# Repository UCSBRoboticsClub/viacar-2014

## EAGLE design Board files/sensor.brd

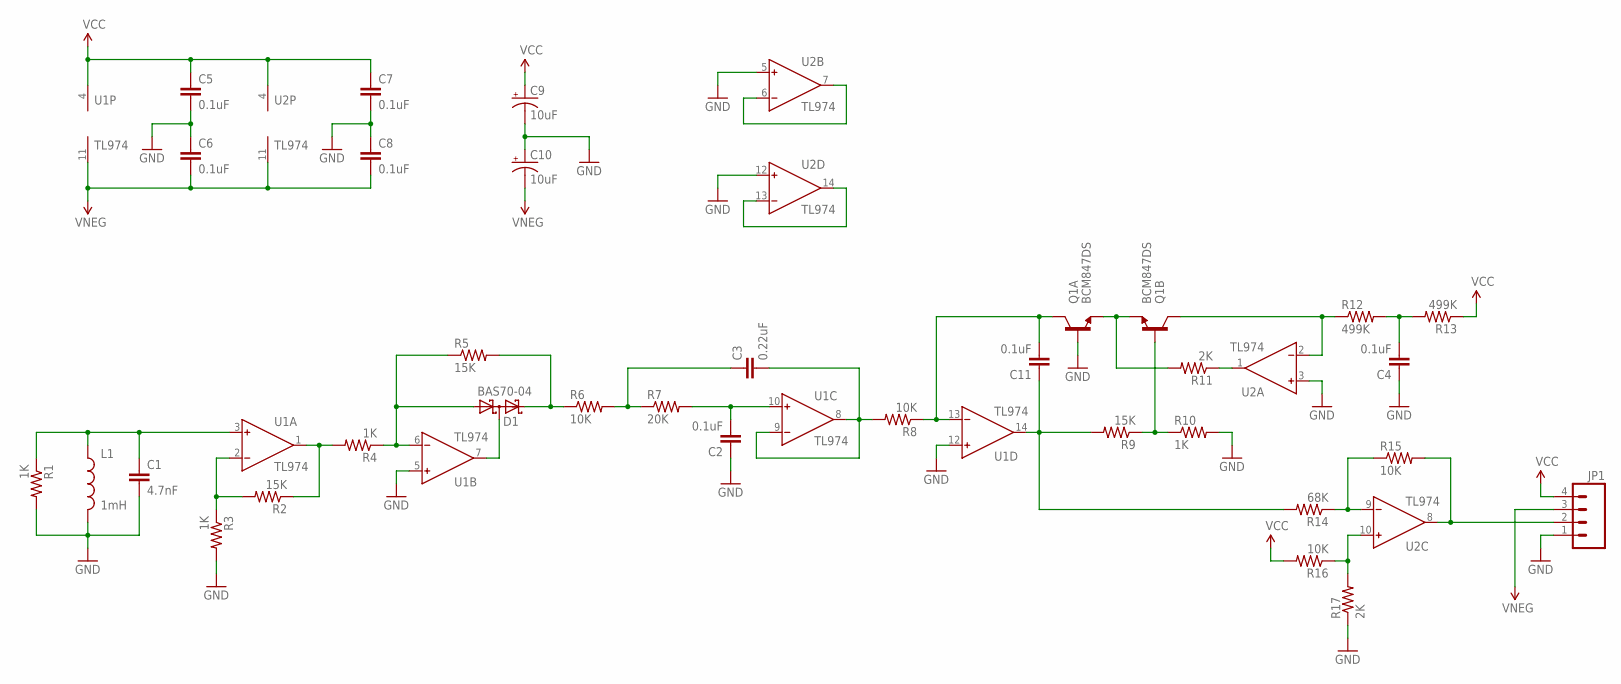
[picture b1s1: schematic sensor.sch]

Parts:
C1: 4.7nF; 0805
C2, C4, C5, C6, C7, C8, C11: 0.1uF; 0805
C3: 0.22uF; 0805
C9, C10: 10uF; E2-4
D1: BAS70-04; SOT23
JP1: M04POLAR_LOCK; MOLEX-1X4_LOCK
L1: 1mH; RLB0912
Q1: BCM847DS; SOT-457
R1, R3, R4, R10: 1K; 0805
R2, R5, R9: 15K; 0805
R6, R8, R15, R16: 10K; 0805
R7: 20K; 0805
R11, R17: 2K; 0805
R12, R13: 499K; 0805
R14: 68K; 0805
U1, U2: TL974; SOIC-14

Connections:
GND: C1.2, C2.1, C4.1, C5.2, C6.1, C7.2, C8.1, C9.-, C10.+, JP1.1, L1.2, Q1.2 (B), R1.2, R3.2, R10.2, R17.1, U1.5 (IN+), U1.12 (IN+), U2.3 (IN+), U2.5 (IN+), U2.12 (IN+)
unnamed: C1.1, L1.1, R1.1, U1.3 (IN+)
unnamed: D1.1 (A1), R4.1, R5.1, U1.6 (IN-)
unnamed: R2.2, R3.1, U1.2 (IN-)
unnamed: R2.1, R4.2, U1.1 (OUT)
unnamed: D1.2 (C2), R5.2, R6.1
unnamed: C2.2, R7.2, U1.10 (IN+)
unnamed: C3.1, R6.2, R7.1
unnamed: D1.3 (C1A2), U1.7 (OUT)
unnamed: U2.6 (IN-), U2.7 (OUT)
unnamed: C3.2, R8.2, U1.8 (OUT), U1.9 (IN-)
unnamed: U2.13 (IN-), U2.14 (OUT)
unnamed: C11.2, Q1.6 (C), R8.1, U1.13 (IN-)
unnamed: R11.1, U2.1 (OUT)
unnamed: Q1.1 (E), Q1.4 (E), R11.2
unnamed: Q1.5 (B), R9.1, R10.1
unnamed: C11.1, R9.2, R14.2, U1.14 (OUT)
unnamed: C4.2, R12.2, R13.2
unnamed: Q1.3 (C), R12.1, U2.2 (IN-)
unnamed: R16.1, R17.2, U2.10 (IN+)
unnamed: R14.1, R15.1, U2.9 (IN-)
unnamed: JP1.2, R15.2, U2.8 (OUT)
VCC: C5.1, C7.1, C9.+, JP1.4, R13.1, R16.2, U1.4 (V+), U2.4 (V+)
VNEG: C6.2, C8.2, C10.-, JP1.3, U1.11 (V-), U2.11 (V-)

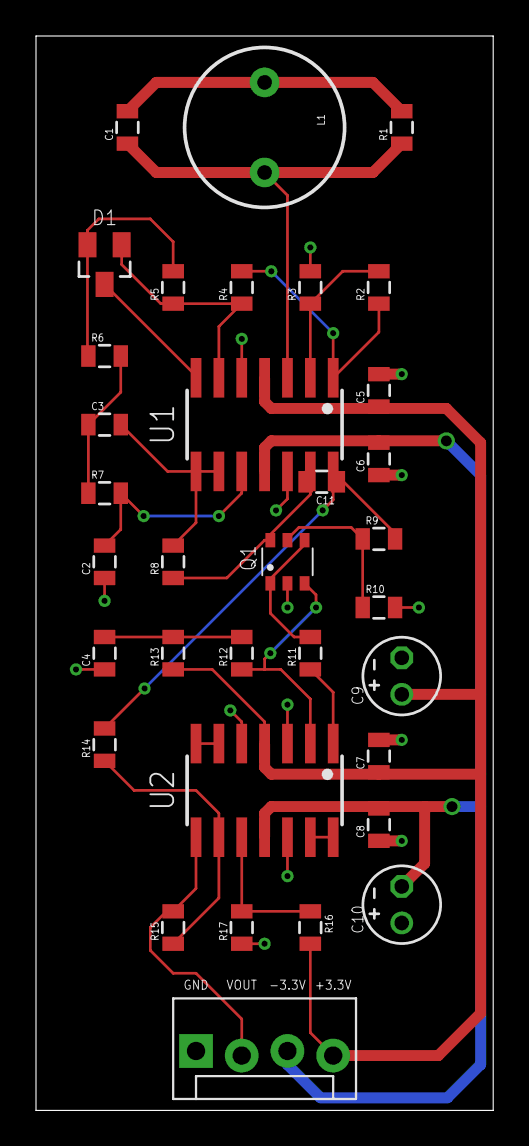
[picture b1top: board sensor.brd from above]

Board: 2 copper layers, 25.4 x 59.7 mm, 34 parts (0 on the bottom side), 24 nets.

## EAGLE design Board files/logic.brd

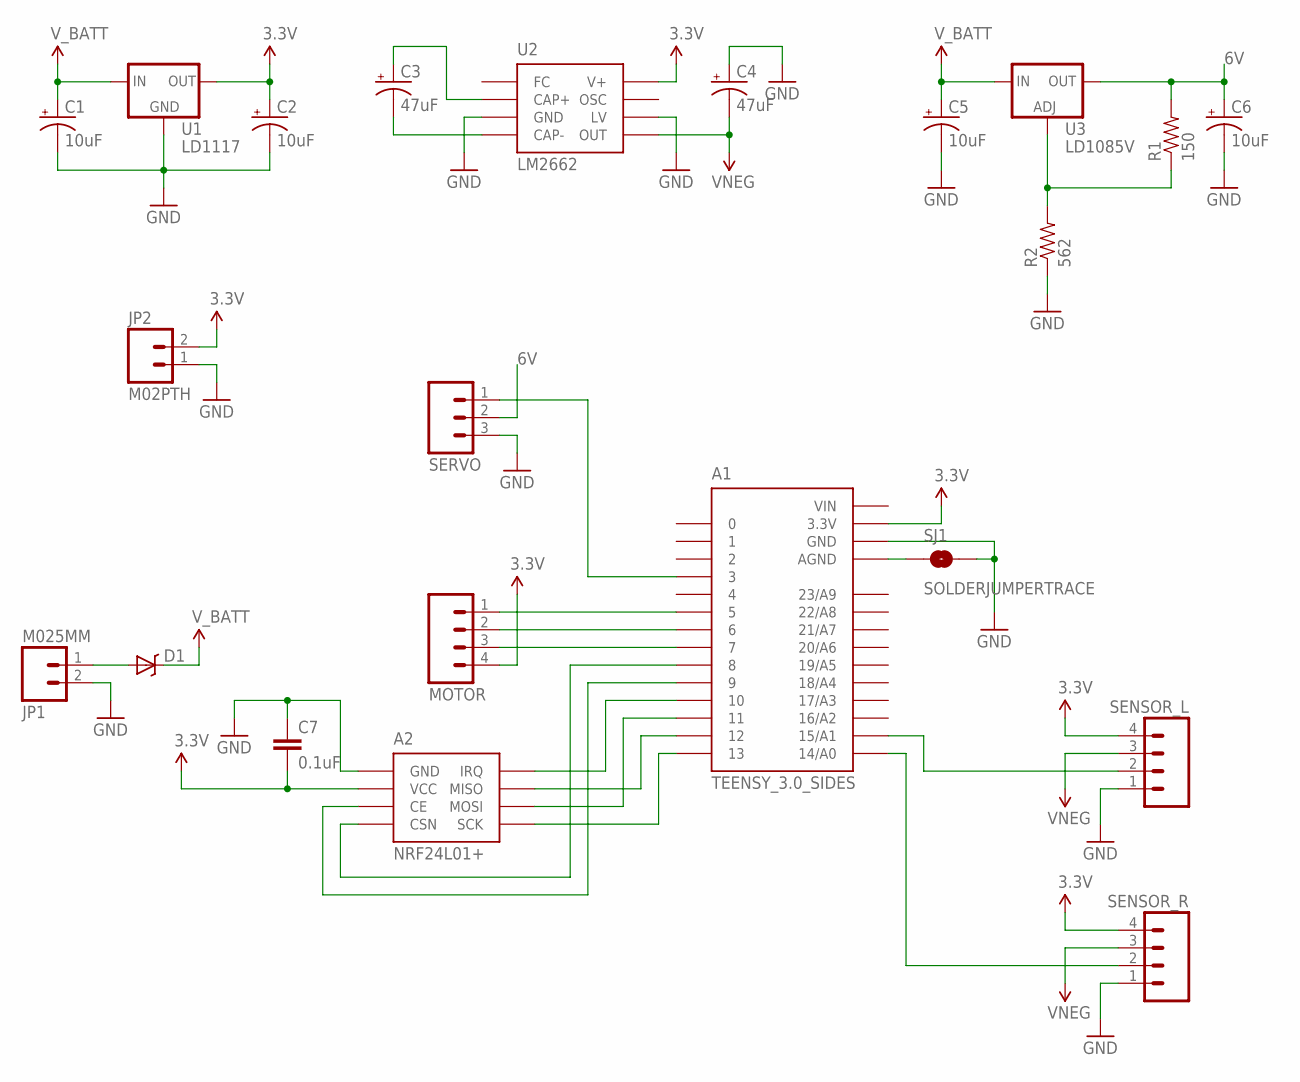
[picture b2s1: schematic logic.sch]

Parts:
A1: TEENSY_3.0_SIDES
A2: NRF24L01+
C1, C2, C5, C6: 10uF; E2-4
C3, C4: 47uF; CPOL-RADIAL-100UF-25V
C7: 0.1uF; 0805
D1: DIODE-SCHOTTKY_; SMA-DIODE
JP1: M025MM; SCREWTERMINAL-5MM-2
JP2: M02PTH; 1X02
MOTOR: M04POLAR_LOCK; MOLEX-1X4_LOCK
R1: 150; 0805
R2: 562; 0805
SENSOR_L: M04POLAR_LOCK; MOLEX-1X4_LOCK
SENSOR_R: M04POLAR_LOCK; MOLEX-1X4_LOCK
SERVO: M03LOCK_LONGPADS; 1X03_LOCK_LONGPADS
SJ1: SOLDERJUMPERTRACE; SJ_2S-TRACE
U1: LD1117; SOT-223
U2: LM2662; SOIC-8
U3: LD1085V; 317TS

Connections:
3.3V: A1.3.3V, A2.2 (VCC), C2.+, C7.2, JP2.2, MOTOR.4, SENSOR_L.4, SENSOR_R.4, U1.2 (OUT), U1.4 (OUT), U2.8 (V+)
6V: C6.+, R1.2, SERVO.2, U3.2 (OUT)
GND: A1.GND, A2.1 (GND), C1.-, C2.-, C4.1 (+), C5.-, C6.-, C7.1, JP1.2, JP2.1, R2.1, SENSOR_L.1, SENSOR_R.1, SERVO.3, SJ1.2, U1.1 (GND), U2.3 (GND), U2.6 (LV)
unnamed: D1.A, JP1.1
unnamed: C3.1 (+), U2.2 (CAP+)
unnamed: C3.2 (-), U2.4 (CAP-)
unnamed: R1.1, R2.2, U3.1 (ADJ)
unnamed: A1.13, A2.5 (SCK)
unnamed: A1.12, A2.7 (MISO)
unnamed: A1.11, A2.6 (MOSI)
unnamed: A1.8, A2.4 (CSN)
unnamed: A1.10, A2.8 (IRQ)
unnamed: A1.9, A2.3 (CE)
unnamed: A1.3, SERVO.1
unnamed: A1.AGND, SJ1.1
unnamed: A1.15/A1, SENSOR_L.2
unnamed: A1.14/A0, SENSOR_R.2
unnamed: A1.5, MOTOR.1
unnamed: A1.6, MOTOR.2
unnamed: A1.7, MOTOR.3
VIN: A1.VIN
VNEG: C4.2 (-), SENSOR_L.3, SENSOR_R.3, U2.5 (OUT)
V_BATT: C1.+, C5.+, D1.C, U1.3 (IN), U3.3 (IN)

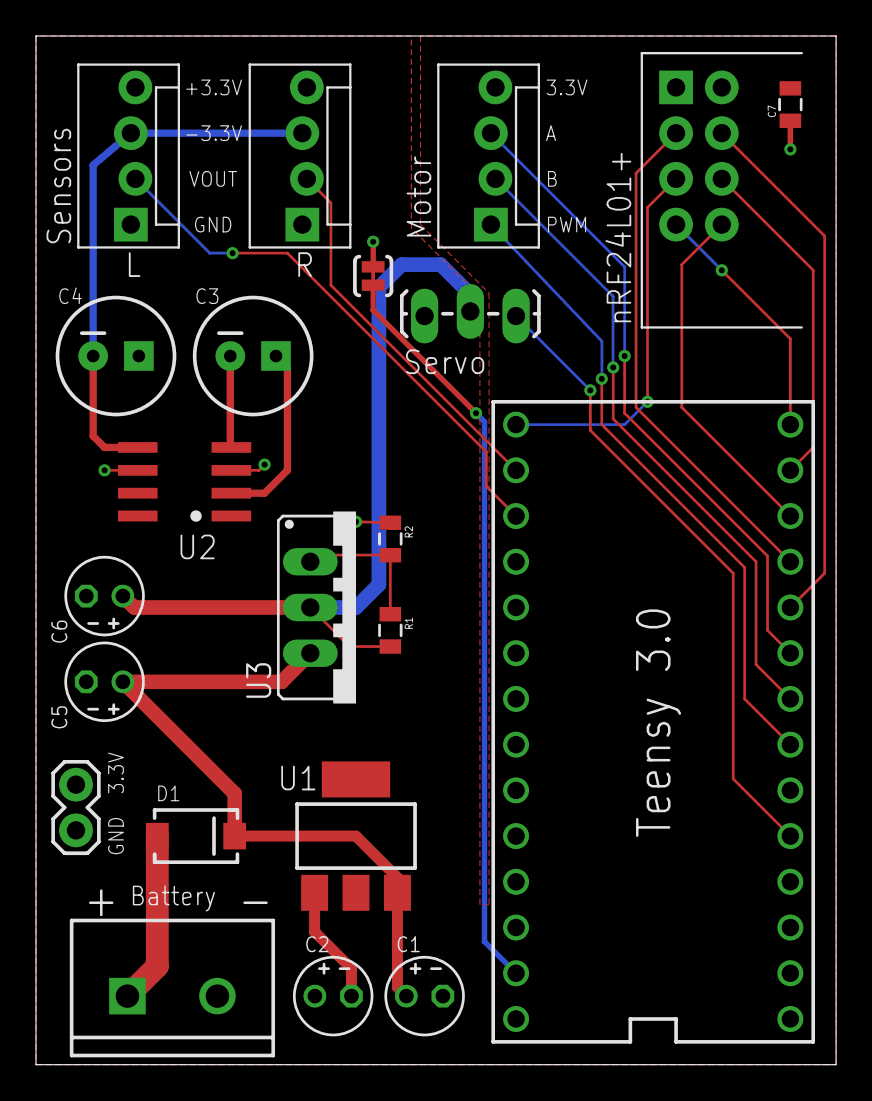
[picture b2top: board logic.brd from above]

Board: 2 copper layers, 44.5 x 57.1 mm, 22 parts (0 on the bottom side), 22 nets.

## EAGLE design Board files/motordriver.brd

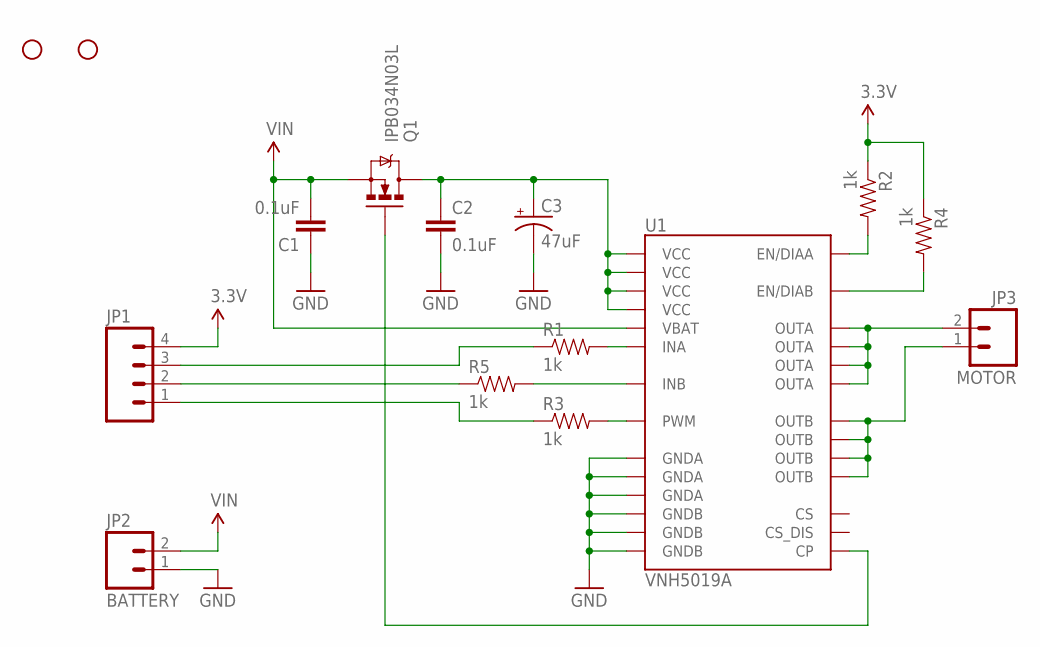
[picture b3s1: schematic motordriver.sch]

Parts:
C1, C2: 0.1uF; 0805
C3: 47uF; CPOL-RADIAL-100UF-25V
JP1: M04POLAR_LOCK; MOLEX-1X4_LOCK
JP2: BATTERY; SCREWTERMINAL-5MM-2
JP3: MOTOR; SCREWTERMINAL-5MM-2
Q1: IPB034N03L; DPAK
R1, R2, R3, R4, R5: 1k; 0805
STANDOFF1, STANDOFF2: STAND-OFF
U1: VNH5019A; MULTIPOWERSO-30

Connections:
3.3V: JP1.4, R2.1, R4.1
GND: C1.1, C2.2, C3.2 (-), JP2.1, U1.18 (GNDB), U1.19 (GNDB), U1.20 (GNDB), U1.26 (GNDA), U1.27 (GNDA), U1.28 (GNDA)
unnamed: R1.2, U1.4 (INA)
unnamed: R5.2, U1.10 (INB)
unnamed: R3.2, U1.7 (PWM)
unnamed: Q1.1 (G), U1.11 (CP)
unnamed: JP1.2, R5.1
unnamed: JP1.3, R1.1
unnamed: JP1.1, R3.1
unnamed: R2.2, U1.5 (EN/DIAA)
unnamed: R4.2, U1.9 (EN/DIAB)
OUTA: JP3.2, U1.1 (OUTA), U1.25 (OUTA), U1.30 (OUTA), U1.SLUG3 (OUTA)
OUTB: JP3.1, U1.15 (OUTB), U1.16 (OUTB), U1.21 (OUTB), U1.SLUG2 (OUTB)
VCC: C2.1, C3.1 (+), Q1.4 (D), U1.3 (VCC), U1.13 (VCC), U1.23 (VCC), U1.SLUG1 (VCC)
VIN: C1.2, JP2.2, Q1.3 (S), U1.12 (VBAT)

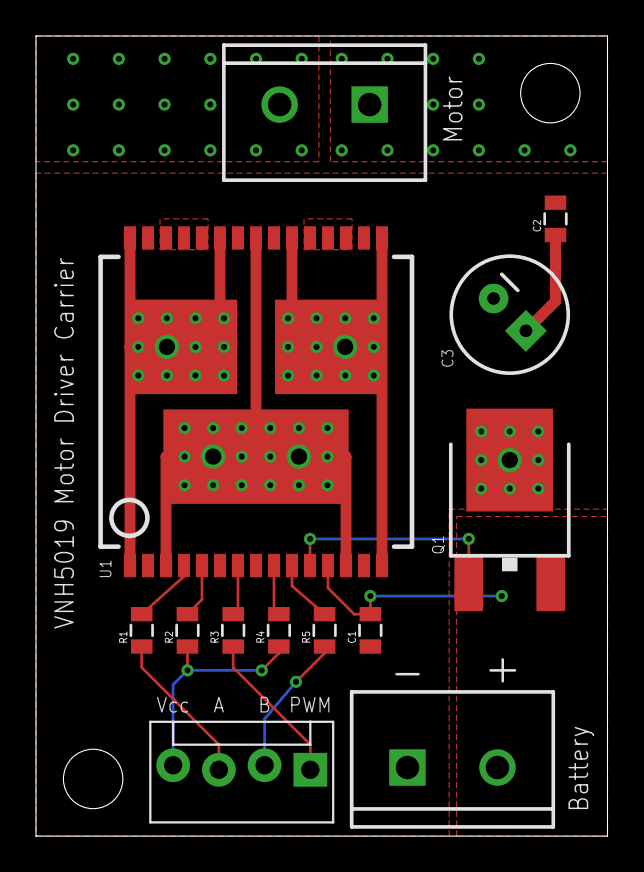
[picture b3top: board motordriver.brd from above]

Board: 2 copper layers, 31.8 x 44.5 mm, 15 parts (0 on the bottom side), 15 nets.

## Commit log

2013-12-21 Motor driver board is complete
2013-12-22 Added sensor board
2013-12-22 Added datasheets and other documents
2013-12-27 Modified motor driver layout
2013-12-27 Added battery polarity labels
    Also cleaned up layout slightly
2013-12-27 Fixed slightly misaligned board outline
2013-12-27 Added labels and removed some thermals
2013-12-27 Made silkscreen orientation consistent
2013-12-29 Significantly modified sensor circuit
2013-12-29 Finished new sensor board layout
2013-12-29 Tweaked ground pour
2013-12-29 Cleaned up wires on motor driver board
2013-12-30 Added component values and removed final rectifier
2013-12-31 Added logic board, schematic is complete
2013-12-31 Added datasheets for new parts and removed unused ones
2013-12-31 Finished logic board layout
2013-12-31 Rerouted servo trace and added labels
2013-12-31 Fixed decoupling caps and added labels
2013-12-31 Added larger decoupling capacitors to the sensor boards
2013-12-31 Increased initial sensor gain from 8 to 256
2014-01-01 Changed logic board layout
2014-01-01 More logic board edits
2014-01-01 Labels are no longer obscured by vias
2014-01-06 Minor logic board changes
2014-01-11 Switched to polarized connectors
    Also added 3.3v out pins on logic board, various other changes
2014-01-12 Modified boards to facilitate mounting
2014-01-12 Added CAD models for board mounts
2014-01-12 Fixed silkscreen positioning
2014-01-12 Moved some components
2014-01-12 Moved a capacitor
2014-01-12 Modified a trace, sending the boards out to manufacture
2014-01-17 Updated solidworks models, added mouting plate drawing
2014-01-28 Slight tweak
2014-02-02 Reduced weight, added better support
2014-02-08 Fixed sensor board bug
    Added a capacitor between U1p13 and U1p14
2014-02-22 Added teensy code
2014-02-23 Made low pass filter class, added load measurement
2014-02-23 Updated the voltage to distance calibration function
2014-02-24 Modified calibration function
    Add automatic detection of vinmax next
2014-03-01 Fixed level shifter resistor values
2014-03-23 Updated terminal to work over serial
    Increased loop frequency to 1 kHz, which puts it at about 25% load
2014-03-23 Added nRF24L01+ datasheet
2014-04-12 Sensor actually works now
2014-04-12 Added calibration code
    Changed lowpass interface
2014-04-13 Changed button interface
2014-04-19 Fixed ControlLoop and error function
2014-04-21 Fixed radio communication
2014-04-26 Fixed clearTimer
2014-04-27 Added data logging, improved radio transmission efficiency
2014-05-04 Added program for calibrating servo

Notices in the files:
parts and their libraries:
SparkFun-DiscreteSemi: Licensing: CC v3.0 Share-Alike You are welcome to use this library for commercial purposes.
